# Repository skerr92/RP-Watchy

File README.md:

# RP-Watchy
This is where you can find the RP Watchy board files, and current firmware.

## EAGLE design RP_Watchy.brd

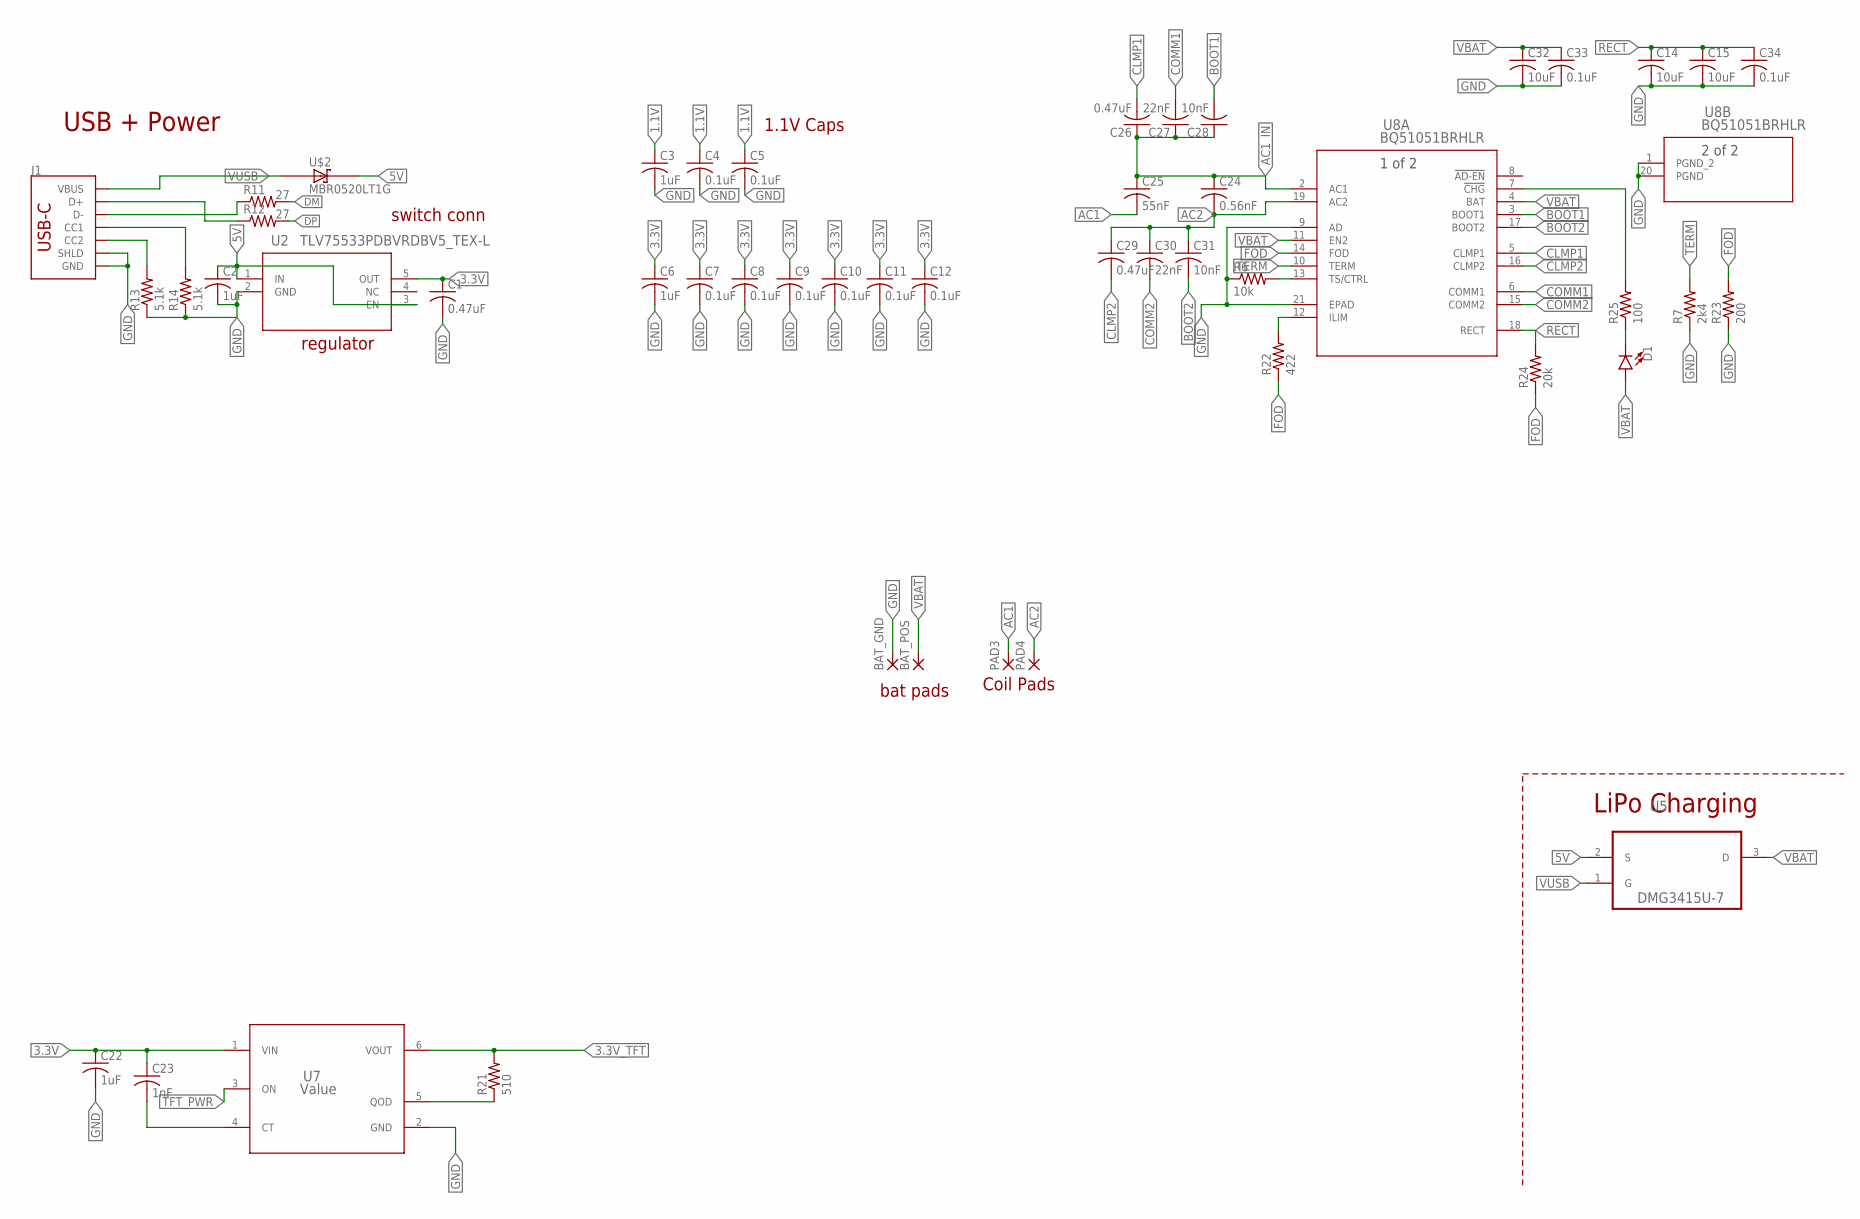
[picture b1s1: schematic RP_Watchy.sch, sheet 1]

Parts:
BAT_GND: SMD2; SMD1,27-2,54
BAT_POS: SMD2; SMD1,27-2,54
C1, C26, C29: 0.47uF; C0402
C2, C3, C6, C22: 1uF; C0402
C4, C5, C7, C8, C9, C10, C11, C12, C33, C34: 0.1uF; C0402
C14, C15, C32: 10uF; C0402
C23: 1nF; C0402
C24: 0.56nF; C0603
C25: 55nF; C0603
C27, C30: 22nF; C0402
C28, C31: 10nF; C0402
D1: LED0603; LED-0603
J1: USB_C_2-LAYER_PADS; USB-C-16P-2LAYER-PADS
PAD3, PAD4: SMD2; SMD1,27-2,54
R6: 10k; R0402
R7: 2k4; R0402
R11, R12: 27; R0603
R13, R14: 5.1k; R0603
R21: 510; R0402
R22: 422; R0402
R23: 200; R0402
R24: 20k; R0402
R25: 100; R0402
U2: TLV75533PDBVRDBV5_TEX-L; DBV5_TEX-L
U5: DMG3415U-7; SOT95P240X105-3N
U7: Value; DBV0006_L
U8: BQ51051BRHLR; RHL20_2P05X3P05
U$2: MBR0520LT1G; SOD3716X117(SOD-123)

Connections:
1.1V: C3.1, C4.1, C5.1; also elsewhere on the board
3.3V: C1.1, C6.1, C7.1, C8.1, C9.1, C10.1, C11.1, C12.1, C22.1, C23.1, U2.5 (OUT), U7.1 (VIN); also elsewhere on the board
3.3V_TFT: R21.2, U7.6 (VOUT); also elsewhere on the board
5V: C2.1, U2.1 (IN), U2.3 (EN), U5.2 (S), U$2.1 (C)
AC1: C25.2, PAD3.1
AC1_IN: C24.1, C25.1, C26.1, C27.1, C28.1, U8.2 (AC1)
AC2: C24.2, C29.1, C30.1, C31.1, PAD4.1, U8.19 (AC2)
BOOT1: C28.2, U8.3 (BOOT1)
BOOT2: C31.2, U8.17 (BOOT2)
CLMP1: C26.2, U8.5 (CLMP1)
CLMP2: C29.2, U8.16 (CLMP2)
COMM1: C27.2, U8.6 (COMM1)
COMM2: C30.2, U8.15 (COMM2)
DM: R11.2; also elsewhere on the board
DP: R12.2; also elsewhere on the board
FOD: R22.1, R23.2, R24.1, U8.14 (FOD)
GND: BAT_GND.1, C1.2, C2.2, C3.2, C4.2, C5.2, C6.2, C7.2, C8.2, C9.2, C10.2, C11.2, C12.2, C14.2, C15.2, C22.2, C32.2, C33.2, C34.2, J1.GND, J1.GND2 (GND), J1.P$1 (SHLD), J1.P$2 (SHLD), J1.P$3 (SHLD), J1.P$4 (SHLD), J1.SHLD1 (SHLD), J1.SHLD2 (SHLD), J1.SHLD3 (SHLD), J1.SHLD4 (SHLD), R6.1, R7.1, R13.1, R14.1, R23.1, U2.2 (GND), U7.2 (GND), U8.1 (PGND_2), U8.9 (AD), U8.20 (PGND), U8.21 (EPAD); also elsewhere on the board
unnamed: R6.2, U8.13 (TS/CTRL)
unnamed: J1.A5 (CC1), R14.2
unnamed: J1.B5 (CC2), R13.2
unnamed: C23.2, U7.4 (CT)
unnamed: R21.1, U7.5 (QOD)
unnamed: R22.2, U8.12 (ILIM)
unnamed: J1.A7 (D-), J1.B7 (D-), R11.1
unnamed: J1.A6 (D+), J1.B6 (D+), R12.1
unnamed: R25.2, U8.7 (!CHG)
unnamed: D1.C, R25.1
RECT: C14.1, C15.1, C34.1, R24.2, U8.18 (RECT)
TERM: R7.2, U8.10 (TERM)
TFT_PWR: U7.3 (ON); also elsewhere on the board
VBAT: BAT_POS.1, C32.1, C33.1, D1.A, U5.3 (D), U8.4 (BAT), U8.11 (EN2)
VUSB: J1.VBUS1 (VBUS), J1.VBUS2 (VBUS), U5.1 (G), U$2.2 (A)

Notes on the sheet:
USB + Power
regulator
bat pads
switch conn
1.1V Caps
LiPo Charging
Coil Pads

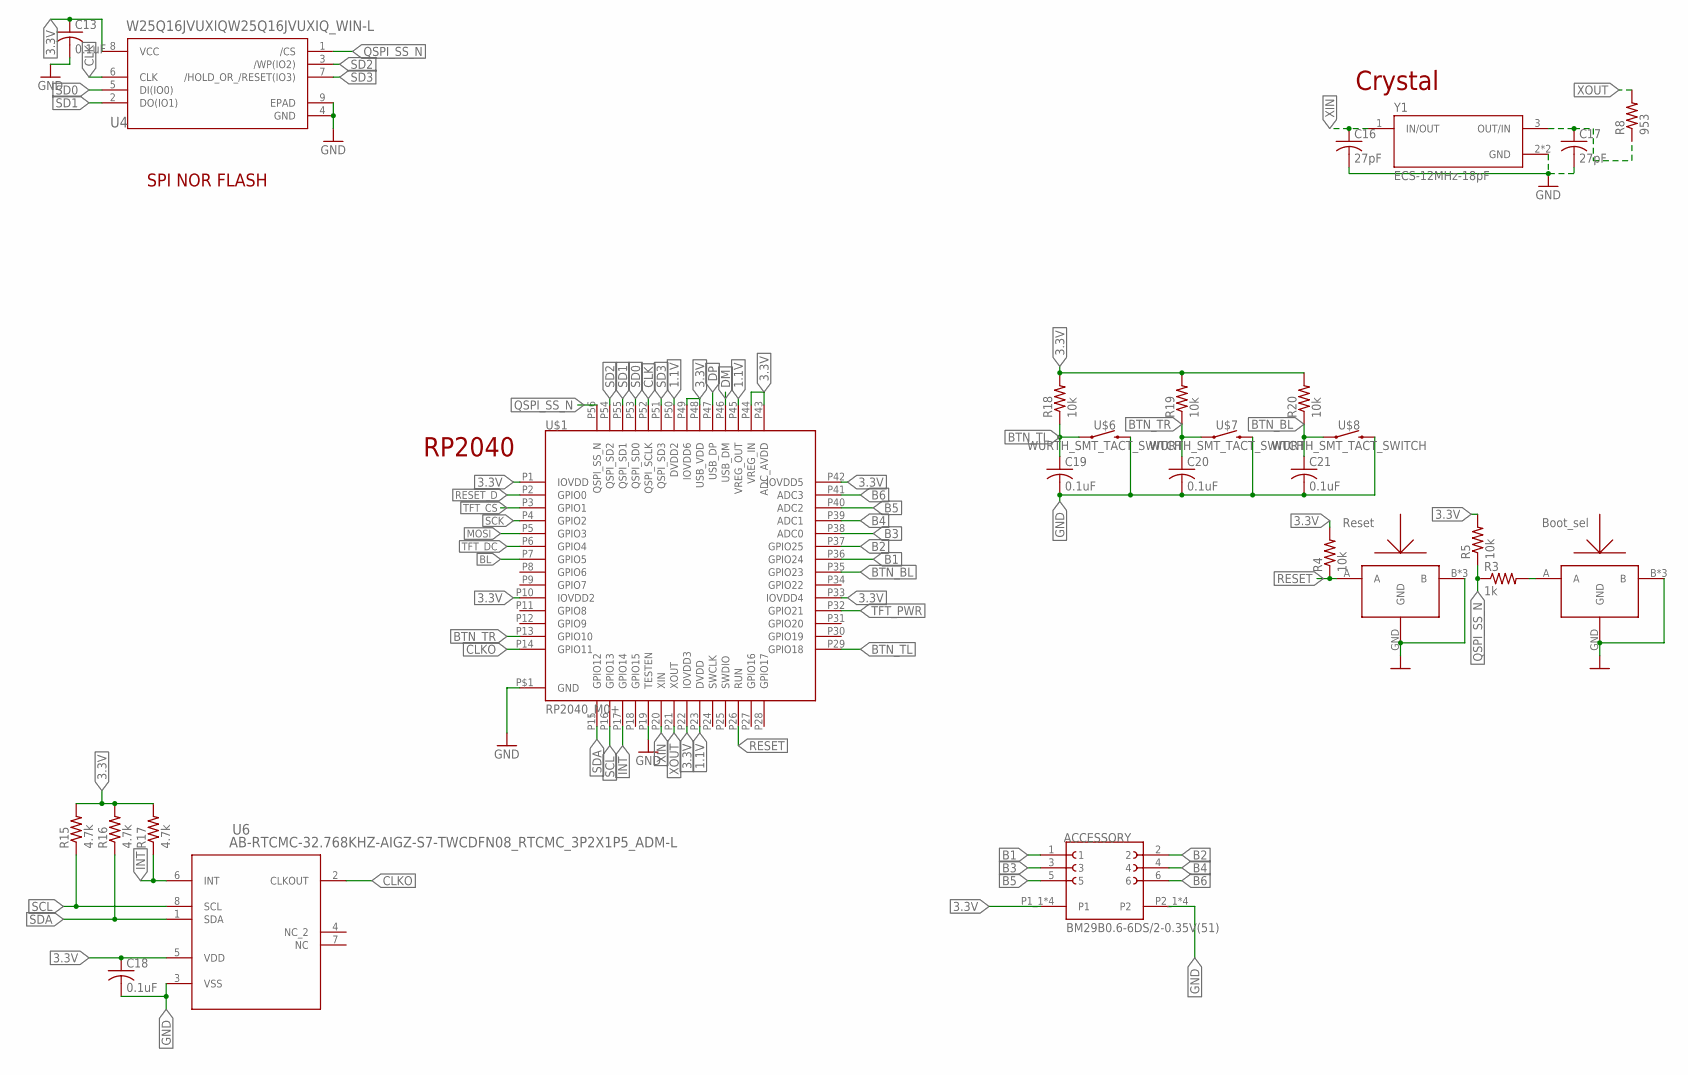
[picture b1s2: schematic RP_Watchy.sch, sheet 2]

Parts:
ACCESSORY: BM29B0.6-6DS/2-0.35V(51); HRS_BM29B0.6-6DS/2-0.35V(51)
C13, C18, C19, C20, C21: 0.1uF; C0402
C16, C17: 27pF; C0402
R3: 1k; R0402
R4, R5, R18, R19, R20: 10k; R0402
R8: 953; R0402
R15, R16, R17: 4.7k; R0402
U4: W25Q16JVUXIQW25Q16JVUXIQ_WIN-L; W25Q16JVUXIQ_WIN-L
U6: AB-RTCMC-32.768KHZ-AIGZ-S7-TWCDFN08_RTCMC_3P2X1P5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; WCDFN08_RTCMC_3P2X1P5_ADM-L
U$1: RP2040_M0+; QFN-56
U$4, U$5: SOF-232HST; 3.3X2.9
U$6, U$7, U$8: WURTH_SMT_TACT_SWITCH; SIDE_MOUNT_SWITCH
Y1: ECS-12MHz-18pF; XTAL_ECS-327ATQMV-AS-TR

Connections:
1.1V: U$1.P23 (DVDD), U$1.P45 (VREG_OUT), U$1.P50 (DVDD2); also elsewhere on the board
3.3V: ACCESSORY.P1_1 (P1), ACCESSORY.P1_2 (P1), ACCESSORY.P1_3 (P1), ACCESSORY.P1_4 (P1), C13.1, C18.1, R4.2, R5.2, R15.2, R16.2, R17.2, R18.2, R19.2, R20.2, U4.8 (VCC), U6.5 (VDD), U$1.P1 (IOVDD), U$1.P10 (IOVDD2), U$1.P22 (IOVDD3), U$1.P33 (IOVDD4), U$1.P42 (IOVDD5), U$1.P43 (ADC_AVDD), U$1.P44 (VREG_IN), U$1.P48 (USB_VDD), U$1.P49 (IOVDD6); also elsewhere on the board
B1: ACCESSORY.1, U$1.P36 (GPIO24)
B2: ACCESSORY.2, U$1.P37 (GPIO25)
B3: ACCESSORY.3, U$1.P38 (ADC0)
B4: ACCESSORY.4, U$1.P39 (ADC1)
B5: ACCESSORY.5, U$1.P40 (ADC2)
B6: ACCESSORY.6, U$1.P41 (ADC3)
BL: U$1.P7 (GPIO5); also elsewhere on the board
BTN_BL: C21.1, R20.1, U$1.P35 (GPIO23), U$8.1
BTN_TL: C19.1, R18.1, U$1.P29 (GPIO18), U$6.1
BTN_TR: C20.1, R19.1, U$1.P13 (GPIO10), U$7.1
CLK: U4.6 (CLK), U$1.P52 (QSPI_SCLK)
CLKO: U6.2 (CLKOUT), U$1.P14 (GPIO11)
DM: U$1.P46 (USB_DM); also elsewhere on the board
DP: U$1.P47 (USB_DP); also elsewhere on the board
GND: ACCESSORY.P2_1 (P2), ACCESSORY.P2_2 (P2), ACCESSORY.P2_3 (P2), ACCESSORY.P2_4 (P2), C13.2, C16.2, C17.2, C18.2, C19.2, C20.2, C21.2, U4.4 (GND), U4.9 (EPAD), U6.3 (VSS), U$1.P19 (TESTEN), U$1.P$1 (GND), U$4.B, U$4.B2 (B), U$4.B3 (B), U$4.GND, U$5.B, U$5.B2 (B), U$5.B3 (B), U$5.GND, U$6.2, U$7.2, U$8.2, Y1.2 (GND), Y1.4 (GND); also elsewhere on the board
INT: R17.1, U6.6 (INT), U$1.P17 (GPIO14)
MOSI: U$1.P5 (GPIO3); also elsewhere on the board
unnamed: R3.2, U$5.A
unnamed: C17.1, R8.1, Y1.3 (OUT/IN)
QSPI_SS_N: R3.1, R5.1, U4.1 (/CS), U$1.P56 (QSPI_SS_N)
RESET: R4.1, U$1.P26 (RUN), U$4.A
RESET_D: U$1.P2 (GPIO0); also elsewhere on the board
SCK: U$1.P4 (GPIO2); also elsewhere on the board
SCL: R15.1, U6.8 (SCL), U$1.P16 (GPIO13)
SD0: U4.5 (DI(IO0)), U$1.P53 (QSPI_SD0)
SD1: U4.2 (DO(IO1)), U$1.P55 (QSPI_SD1)
SD2: U4.3 (/WP(IO2)), U$1.P54 (QSPI_SD2)
SD3: U4.7 (/HOLD_OR_/RESET(IO3)), U$1.P51 (QSPI_SD3)
SDA: R16.1, U6.1 (SDA), U$1.P15 (GPIO12)
TFT_CS: U$1.P3 (GPIO1); also elsewhere on the board
TFT_DC: U$1.P6 (GPIO4); also elsewhere on the board
TFT_PWR: U$1.P32 (GPIO21); also elsewhere on the board
XIN: C16.1, U$1.P20 (XIN), Y1.1 (IN/OUT)
XOUT: R8.2, U$1.P21 (XOUT)

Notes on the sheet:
RP2040
SPI NOR FLASH
Crystal
Reset
Boot_sel

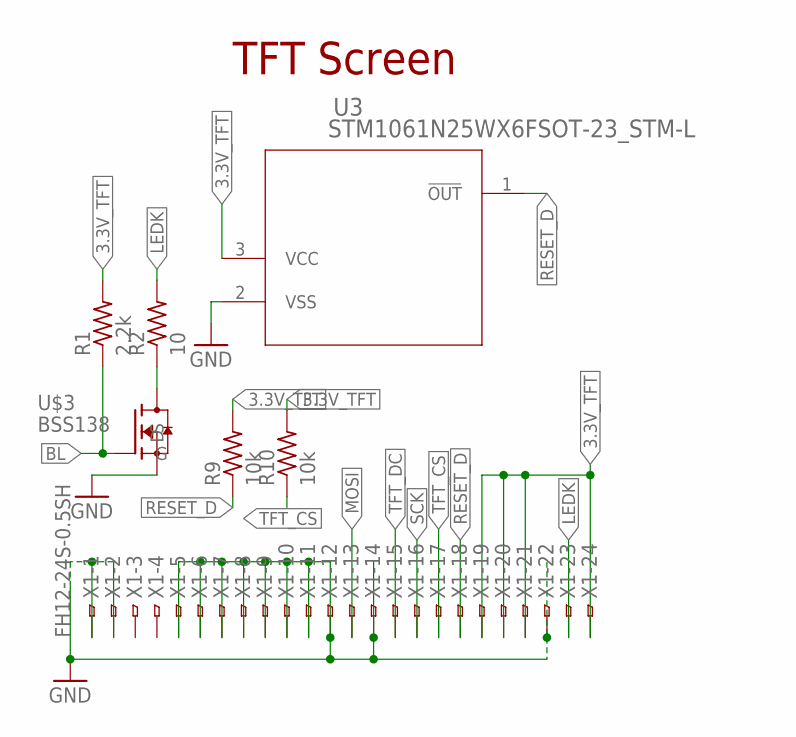
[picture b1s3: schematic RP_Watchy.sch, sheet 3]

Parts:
R1: 2.2k; R0603
R2: 10; R0402
R9, R10: 10k; R0402
U3: STM1061N25WX6FSOT-23_STM-L; SOT-23_STM-L
U$3: BSS138
X1: FH12-24S-0.5SH

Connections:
3.3V_TFT: R1.2, R9.2, R10.2, U3.3 (VCC), X1.19, X1.20, X1.21, X1.24; also elsewhere on the board
BL: R1.1, U$3.G; also elsewhere on the board
GND: U3.2 (VSS), U$3.S, X1.1, X1.2, X1.5, X1.6, X1.7, X1.8, X1.9, X1.10, X1.11, X1.12, X1.14, X1.22; also elsewhere on the board
LEDK: R2.2, X1.23
MOSI: X1.13; also elsewhere on the board
unnamed: R2.1, U$3.D
RESET_D: R9.1, U3.1 (!OUT), X1.18; also elsewhere on the board
SCK: X1.16; also elsewhere on the board
TFT_CS: R10.1, X1.17; also elsewhere on the board
TFT_DC: X1.15; also elsewhere on the board

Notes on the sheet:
TFT Screen

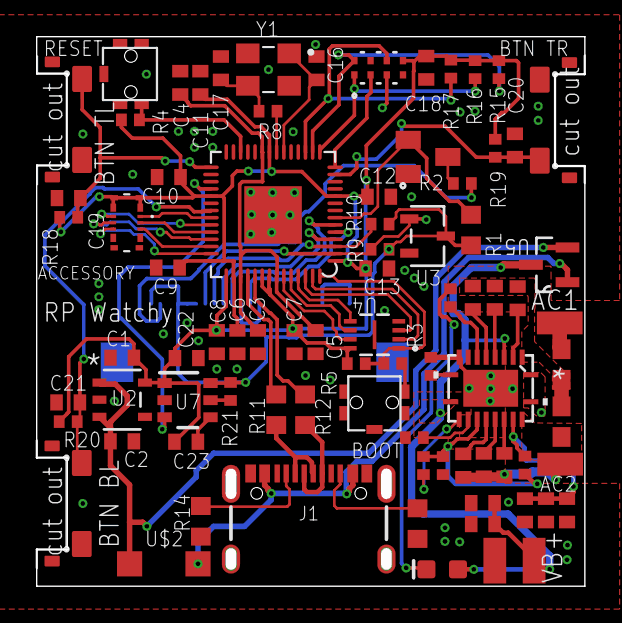
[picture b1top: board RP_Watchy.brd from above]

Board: 2 copper layers, 29.9 x 30.0 mm, 83 parts (1 on the bottom side), 64 nets.

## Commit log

2023-06-30 adding board and schematic files
2023-06-30 Create README. md

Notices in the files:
parts and their libraries:
SparkFun-Connectors: Licensing: Creative Commons ShareAlike 4.0 International - https://creativecommons.org/licenses/by-sa/4.0
COPYRIGHT: Copyright (C) 2018 Accelerated Designs. All rights reserved
COPYRIGHT: Copyright (C) 2021 Ultra Librarian. All rights reserved.
